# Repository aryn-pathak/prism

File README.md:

# The Prism Flight Controller
## An STM32F401CCU6 based flight controller integrating BMP388 barometer and ICM-42688-P gyroscopic sensor, measuring just 2.5 x 2.5cm. 

### Images:

NOTE: work in progress, full project is aiming to have custom Prism firmware and a full drone build.

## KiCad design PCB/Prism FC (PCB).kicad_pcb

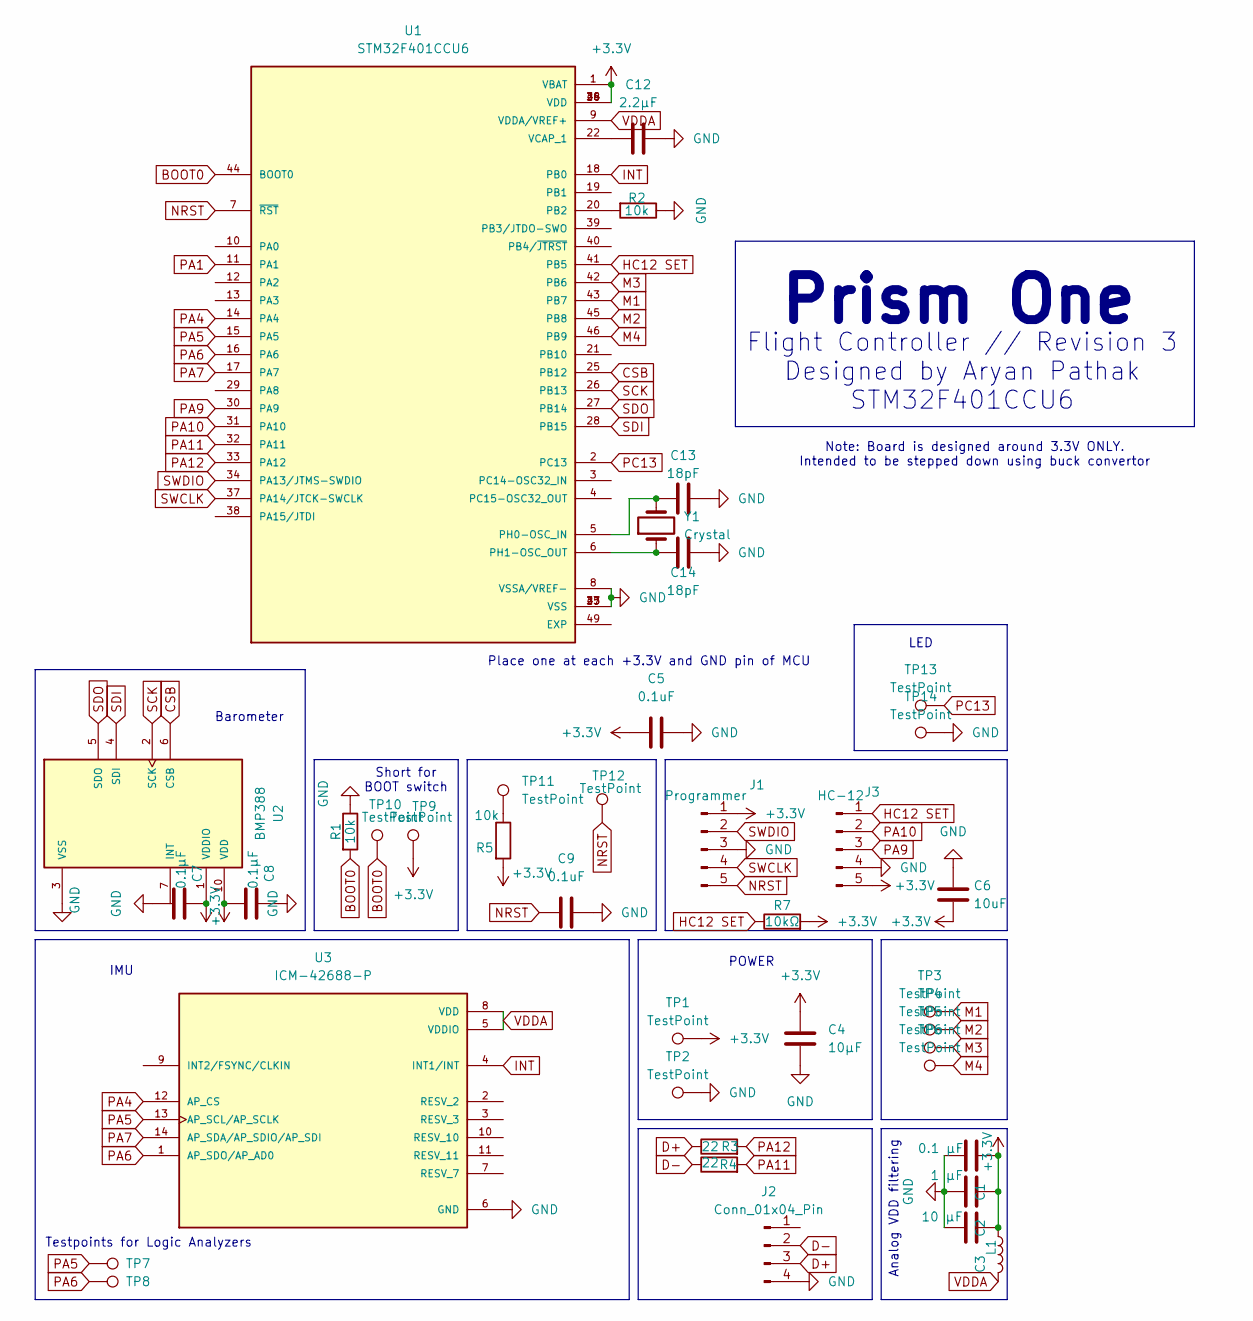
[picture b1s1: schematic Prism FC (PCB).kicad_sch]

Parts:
C1: 0.1 µF; C_0603_1608Metric
C2: 1 µF; C_0603_1608Metric
C3: 10 µF; C_0805_2012Metric
C4: 10µF; C_0805_2012Metric
C5, C9: 0.1uF; C_0603_1608Metric
C6: 10uF; C_0805_2012Metric
C7, C8: 0.1µF; C_0603_1608Metric
C12: 2.2µF; C_0805_2012Metric
C13, C14: 18pF; C_0603_1608Metric
J1: Programmer; PinHeader_1x05_P1.00mm_Vertical
J2: Conn_01x04_Pin; PinHeader_1x04_P1.00mm_Vertical
J3: HC-12; PinHeader_1x05_P1.00mm_Vertical
L1: L; R_0603_1608Metric
R1, R2, R5: 10k; R_0603_1608Metric
R3, R4: 22; R_0603_1608Metric
R7: 10kΩ; R_0603_1608Metric
TP1, TP2: TestPoint; TestPoint_THTPad_2.5x2.5mm_Drill1.2mm
TP3, TP4, TP5, TP6: TestPoint; TestPoint_Pad_1.5x1.5mm
TP7, TP8, TP9, TP10, TP11, TP12, TP13, TP14: TestPoint; TestPoint_Pad_D1.0mm
U1: STM32F401CCU6; PARTREV 11
U2: BMP388; 10LGA_2X2X0p75_BOS; PARTREV 1.1
U3: ICM-42688-P; PARTREV 1.2
Y1: Crystal; Crystal_SMD_Abracon_ABM7-2Pin_6.0x3.5mm

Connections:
+3.3V: C1.1, C2.1, C3.1, C4.1, C5.1, C6.2, C7.1, C8.2, J1.1, J3.5, L1.1, R5.2, R7.2, TP1.1, TP9.1, U1.1 (VBAT), U1.24 (VDD), U1.36 (VDD), U1.48 (VDD), U2.1 (VDDIO), U2.10 (VDD); also elsewhere on the board
BOOT0: R1.2, TP10.1, U1.44 (BOOT0)
CSB: U1.25 (PB12), U2.6 (CSB)
D+: J2.3, R3.1
D-: J2.2, R4.1
GND: C1.2, C2.2, C3.2, C4.2, C5.2, C6.1, C7.2, C8.1, C9.2, C12.2, C13.2, C14.2, J1.3, J2.4, J3.4, R1.1, R2.1, TP2.1, TP14.1, U1.8 (VSSA/VREF-), U1.23 (VSS), U1.35 (VSS), U1.47 (VSS), U1.49 (EXP), U2.3 (VSS), U2.8 (VSS), U2.9 (VSS), U3.6 (GND); also elsewhere on the board
HC12 SET: J3.1, R7.1, U1.41 (PB5)
INT: U1.18 (PB0), U3.4 (INT1/INT)
M1: TP3.1, U1.43 (PB7)
M2: TP4.1, U1.45 (PB8)
M3: TP5.1, U1.42 (PB6)
M4: TP6.1, U1.46 (PB9)
NRST: C9.1, J1.5, TP12.1, U1.7 (~RST)
unnamed: R5.1, TP11.1
unnamed: C13.1, U1.5 (PH0-OSC_IN), Y1.2
unnamed: C14.1, U1.6 (PH1-OSC_OUT), Y1.1
unnamed: C12.1, U1.22 (VCAP_1)
PA1: U1.11 (PA1)
PA4: U1.14 (PA4), U3.12 (AP_CS)
PA5: TP7.1, U1.15 (PA5), U3.13 (AP_SCL/AP_SCLK)
PA6: TP8.1, U1.16 (PA6), U3.1 (AP_SDO/AP_AD0)
PA7: U1.17 (PA7), U3.14 (AP_SDA/AP_SDIO/AP_SDI)
PA9: J3.3, U1.30 (PA9)
PA10: J3.2, U1.31 (PA10)
PA11: R4.2, U1.32 (PA11)
PA12: R3.2, U1.33 (PA12)
PB2: R2.2, U1.20 (PB2)
PC13: TP13.1, U1.2 (PC13)
SCK: U1.26 (PB13), U2.2 (SCK)
SDI: U1.28 (PB15), U2.4 (SDI)
SDO: U1.27 (PB14), U2.5 (SDO)
SWCLK: J1.4, U1.37 (PA14/JTCK-SWCLK)
SWDIO: J1.2, U1.34 (PA13/JTMS-SWDIO)
VDDA: L1.2, U1.9 (VDDA/VREF+), U3.5 (VDDIO), U3.8 (VDD)

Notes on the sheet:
Analog VDD filtering
POWER
Short for BOOT switch
Prism One
LED
Testpoints for Logic Analyzers
Flight Controller // Revision 3 Designed by Aryan Pathak STM32F401CCU6
Note: Board is designed around 3.3V ONLY. Intended to be stepped down using buck convertor
IMU
Place one at each +3.3V and GND pin of MCU
Barometer

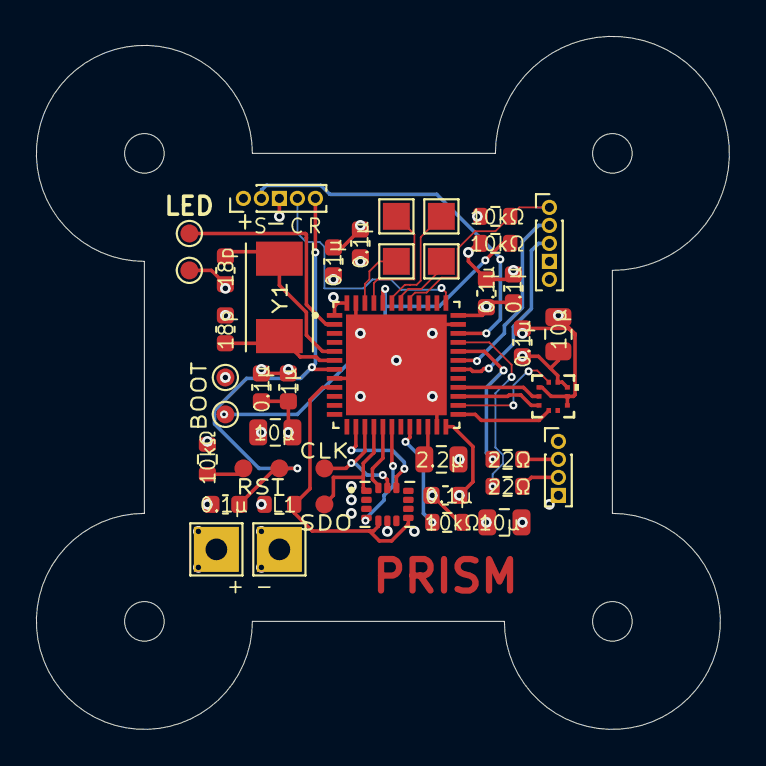
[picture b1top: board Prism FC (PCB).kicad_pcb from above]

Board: 4 copper layers, 38.5 x 38.5 mm, 43 parts (0 on the bottom side), 33 nets.

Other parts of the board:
C5#2, C5#3, C5#4: 0.1uF; C_0603_1608Metric

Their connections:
+3.3V: C5#2.1, C5#3.1, C5#4.1; also elsewhere on the board
GND: C5#2.2, C5#3.2, C5#4.2; also elsewhere on the board

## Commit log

2025-12-26 gonna add new PCB and schematic files, cleaning up structure too
2025-12-26 removed old FC step model
2025-12-26 folder
2025-12-27 Rename THRUST assembly.zip to assembly.zip
2025-12-28 delete
2025-12-28 added PCB file
